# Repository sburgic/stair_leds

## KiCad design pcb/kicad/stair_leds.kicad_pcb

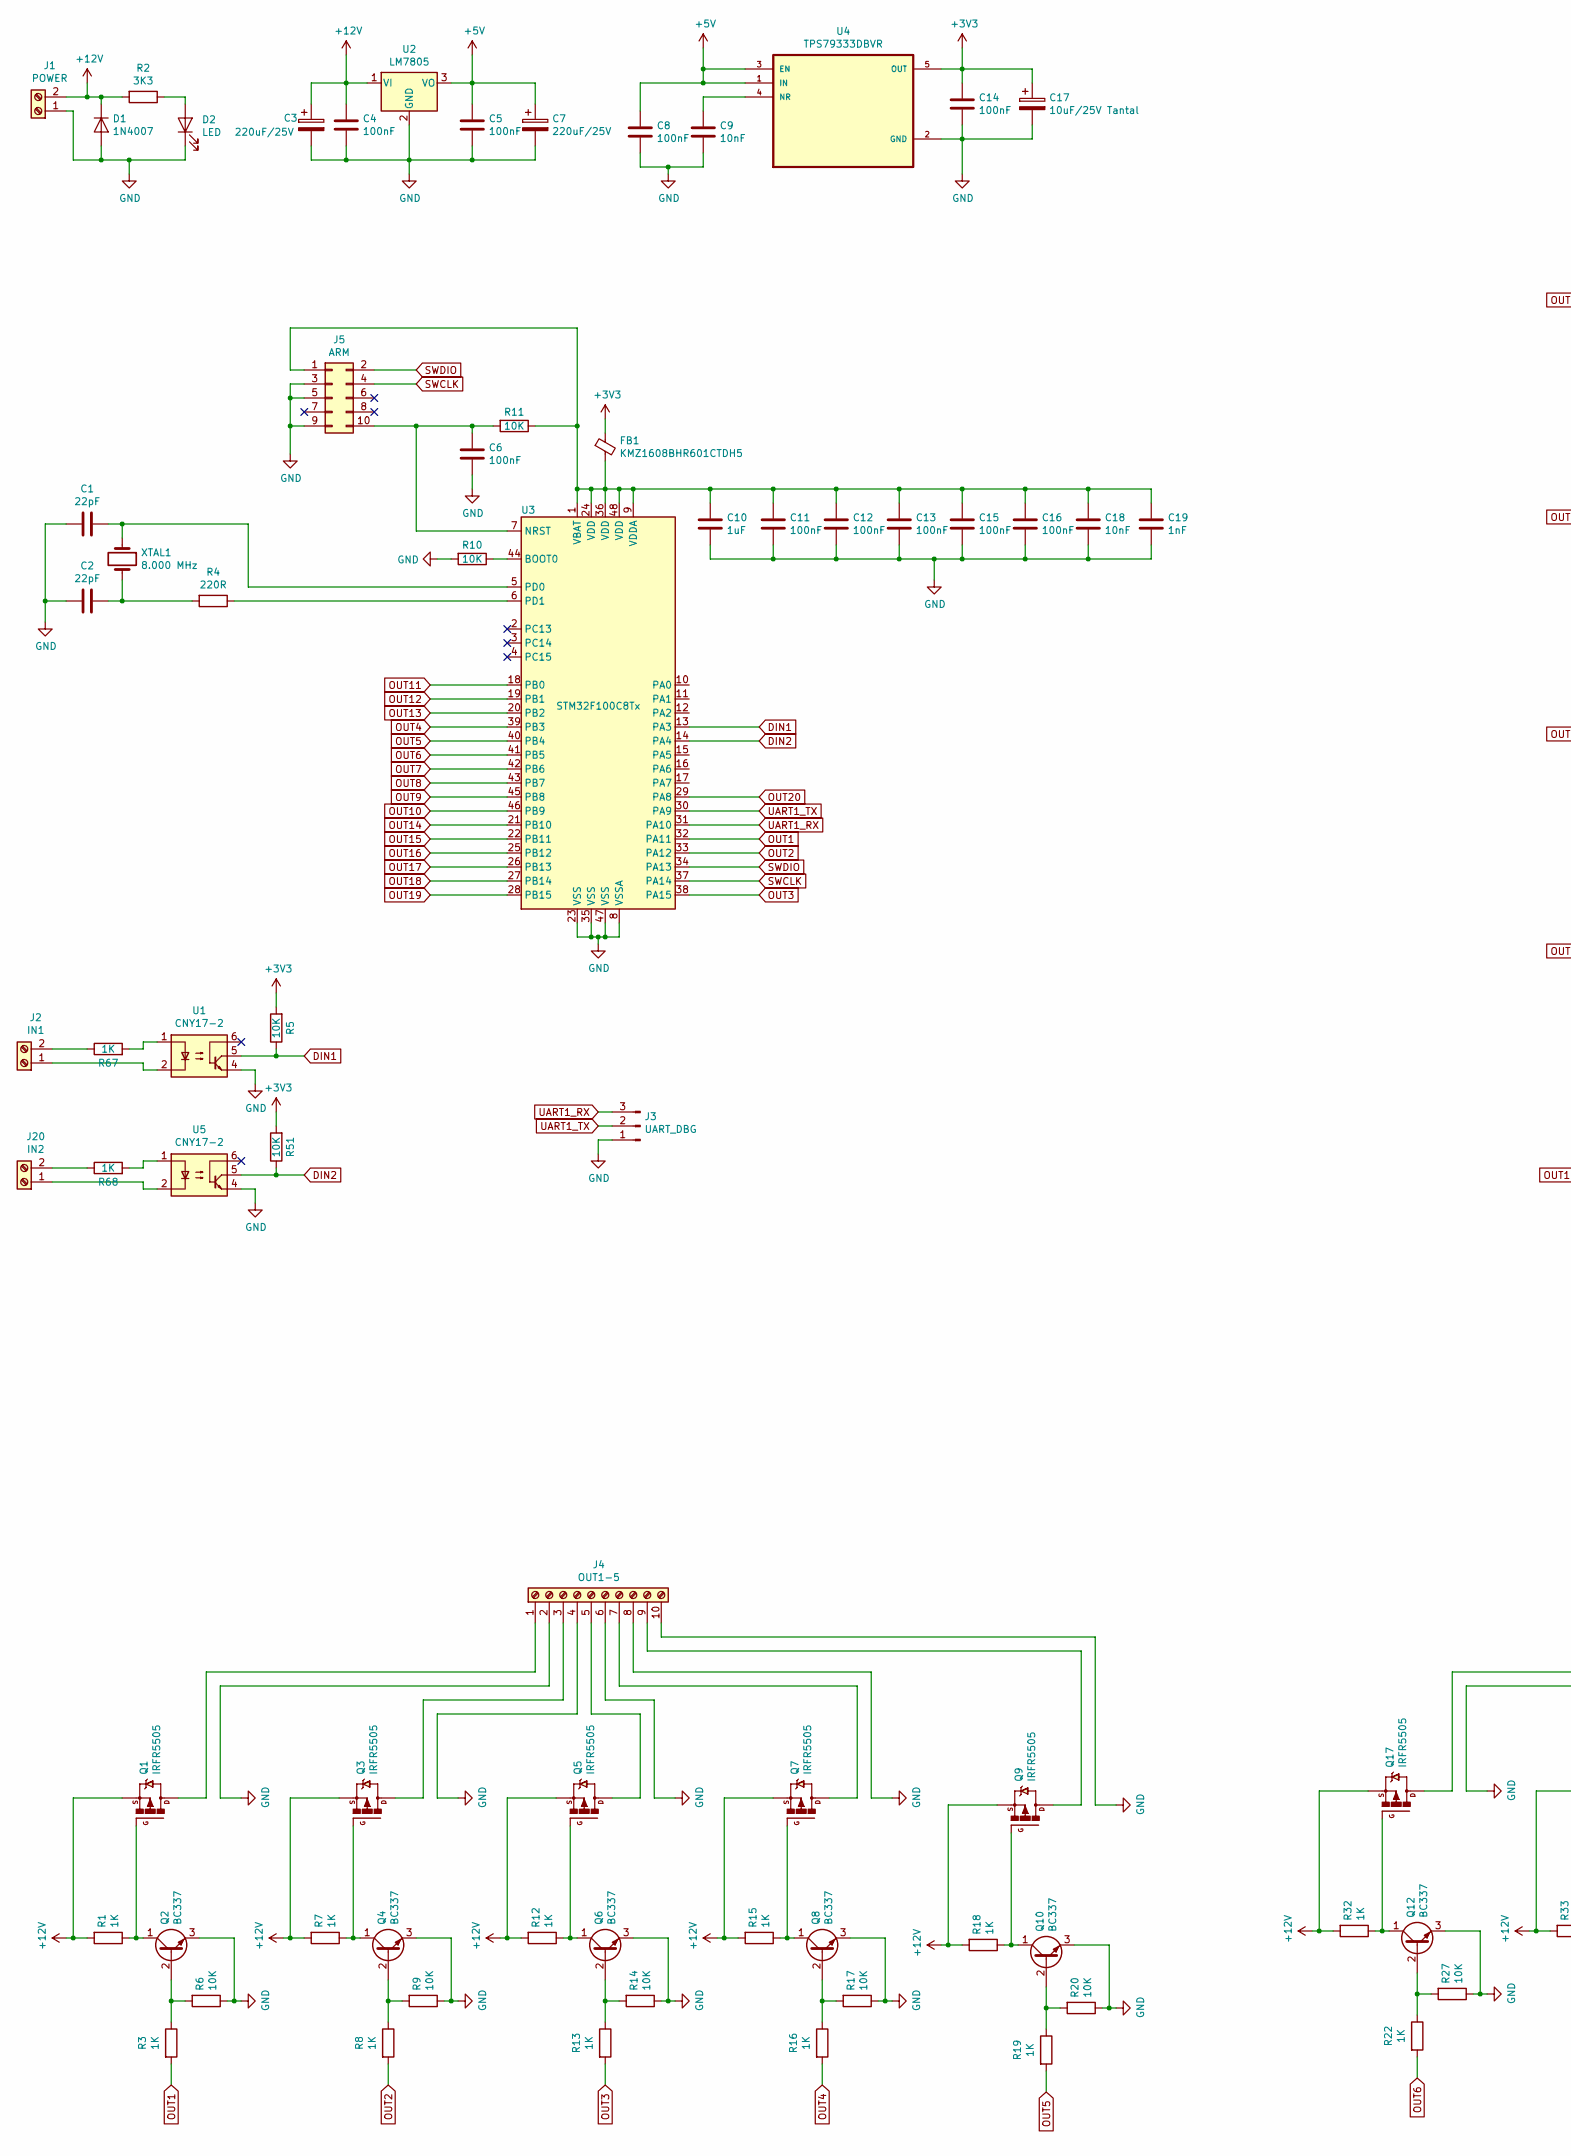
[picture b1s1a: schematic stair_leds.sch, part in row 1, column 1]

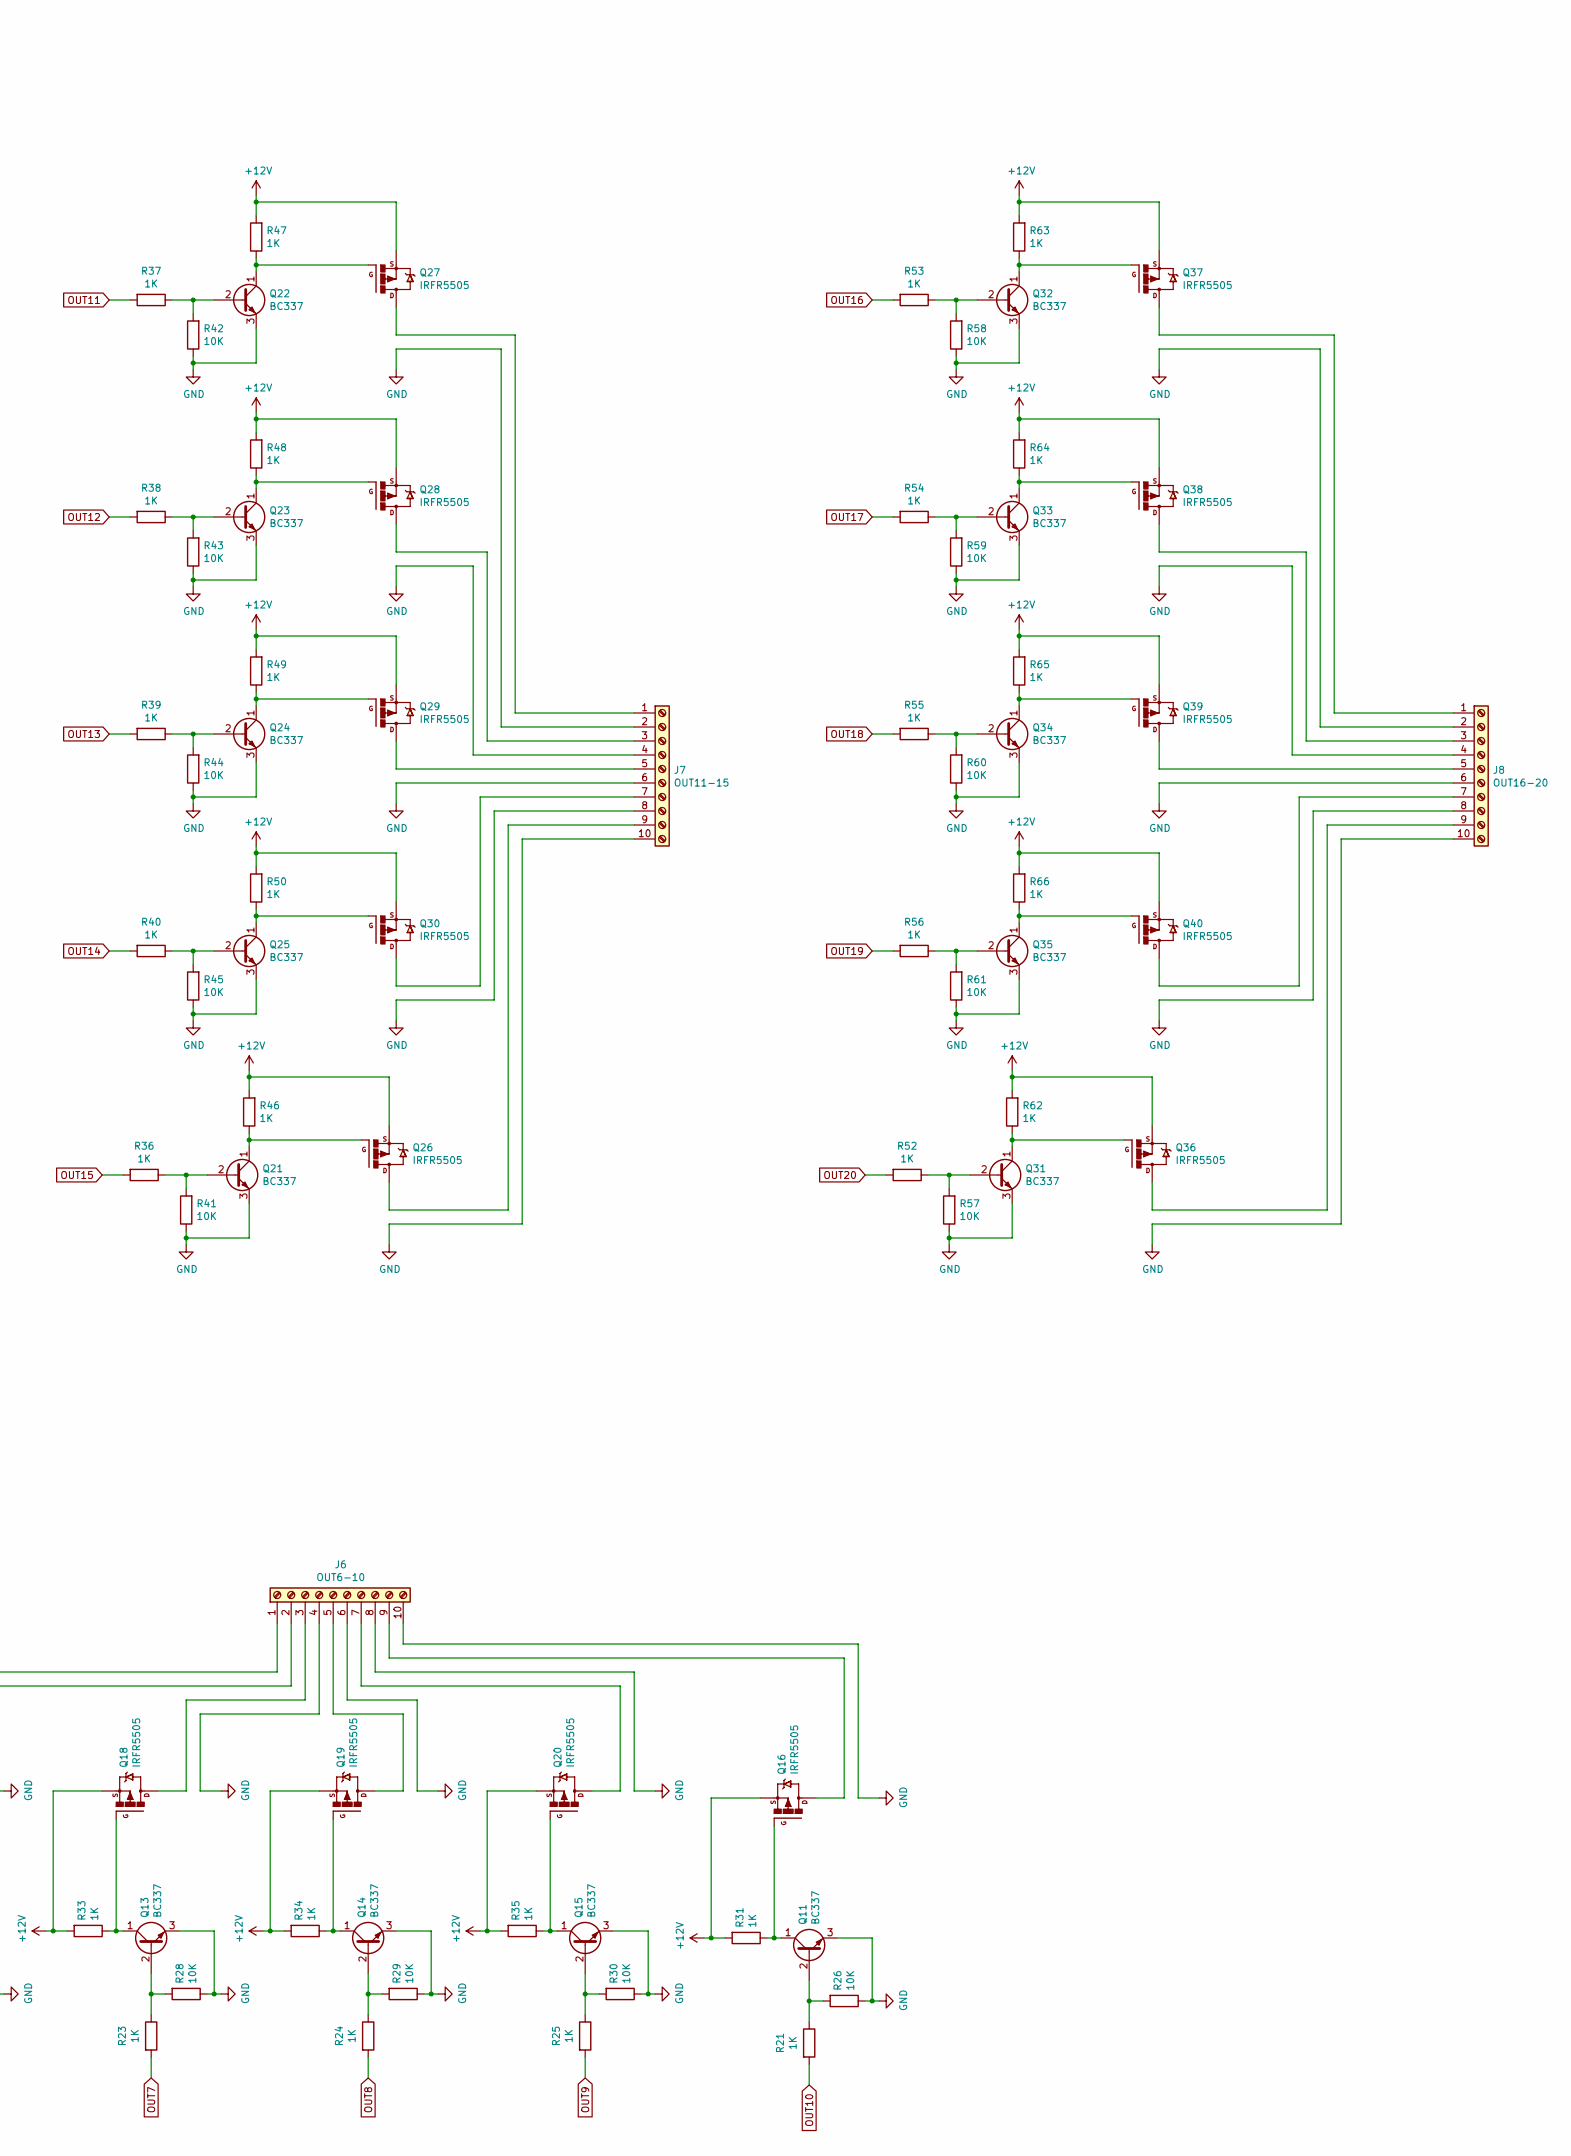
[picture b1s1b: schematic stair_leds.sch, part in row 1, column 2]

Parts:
C1, C2: 22pF; C_Disc_D3.0mm_W1.6mm_P2.50mm
C3, C7: 220uF/25V; CP_Radial_D10.0mm_P5.00mm
C4, C5, C6, C8, C11, C12, C13, C14, C15, C16: 100nF; C_0603_1608Metric_Pad1.05x0.95mm_HandSolder
C9, C18: 10nF; C_0603_1608Metric_Pad1.05x0.95mm_HandSolder
C10: 1uF; C_0805_2012Metric_Pad1.15x1.40mm_HandSolder
C17: 10uF/25V Tantal; C_1210_3225Metric_Pad1.42x2.65mm_HandSolder
C19: 1nF; C_0603_1608Metric_Pad1.05x0.95mm_HandSolder
D1: 1N4007; D_DO-41_SOD81_P10.16mm_Horizontal
D2: LED; LED_D3.0mm
FB1: KMZ1608BHR601CTDH5; C_0805_2012Metric_Pad1.15x1.40mm_HandSolder
J1: POWER; TerminalBlock_MetzConnect_Type011_RT05502HBWC_1x02_P5.00mm_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
J2: IN1; TerminalBlock_MetzConnect_Type011_RT05502HBWC_1x02_P5.00mm_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
J3: UART_DBG; PinHeader_1x03_P2.54mm_Vertical
J4: OUT1-5; TerminalBlock_RND_205-00009_1x10_P5.00mm_Horizontal
J5: ARM; PinHeader_2x05_P1.27mm_Vertical
J6: OUT6-10; TerminalBlock_RND_205-00009_1x10_P5.00mm_Horizontal
J7: OUT11-15; TerminalBlock_RND_205-00009_1x10_P5.00mm_Horizontal
J8: OUT16-20; TerminalBlock_RND_205-00009_1x10_P5.00mm_Horizontal
J20: IN2; TerminalBlock_MetzConnect_Type011_RT05502HBWC_1x02_P5.00mm_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
Q1, Q3, Q5, Q7, Q9, Q16, Q17, Q18, Q19, Q20, Q26, Q27, Q28, Q29, Q30, Q36, Q37, Q38, Q39, Q40: IRFR5505; DPAK
Q2, Q4, Q6, Q8, Q10, Q11, Q12, Q13, Q14, Q15, Q21, Q22, Q23, Q24, Q25, Q31, Q32, Q33, Q34, Q35: BC337; TO-92_Inline_Wide
R1, R3, R7, R8, R12, R13, R15, R16, R18, R19, R21, R22, R23, R24, R25, R31, R32, R33, R34, R35, R36, R37, R38, R39, R40, R46, R47, R48, R49, R50, R52, R53, R54, R55, R56, R62, R63, R64, R65, R66, R67, R68: 1K; R_0805_2012Metric_Pad1.15x1.40mm_HandSolder
R2: 3K3; R_0805_2012Metric_Pad1.15x1.40mm_HandSolder
R4: 220R; R_0805_2012Metric_Pad1.15x1.40mm_HandSolder
R5, R6, R9, R10, R11, R14, R17, R20, R26, R27, R28, R29, R30, R41, R42, R43, R44, R45, R51, R57, R58, R59, R60, R61: 10K; R_0805_2012Metric_Pad1.15x1.40mm_HandSolder
U1, U5: CNY17-2; DIP-6_W7.62mm
U2: LM7805; TO-220-3_Vertical
U3: STM32F100C8Tx; LQFP-48_7x7mm_P0.5mm
U4: TPS79333DBVR; SOT95P280X145-5N
XTAL1: 8.000 MHz; Crystal_SMD_HC49-SD

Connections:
+3V3: C14.1, C17.1, FB1.1, R5.2, R51.2, U4.5 (OUT)
+5V: C5.1, C7.1, C8.1, U2.3 (VO), U4.1 (IN), U4.3 (EN)
+12V: C3.1, C4.1, D1.1 (K), J1.2, Q1.3, Q3.3, Q5.3, Q7.3, Q9.3, Q16.3, Q17.3, Q18.3, Q19.3, Q20.3, Q26.3, Q27.3, Q28.3, Q29.3, Q30.3, Q36.3, Q37.3, Q38.3, Q39.3, Q40.3, R1.2, R2.2, R7.2, R12.2, R15.2, R18.2, R31.2, R32.2, R33.2, R34.2, R35.2, R46.2, R47.2, R48.2, R49.2, R50.2, R62.2, R63.2, R64.2, R65.2, R66.2, U2.1 (VI)
DIN1: R5.1, U1.5, U3.13 (PA3)
DIN2: R51.1, U3.14 (PA4), U5.5
GND: C1.2, C2.2, C3.2, C4.2, C5.2, C6.2, C7.2, C8.2, C9.2, C10.2, C11.2, C12.2, C13.2, C14.2, C15.2, C16.2, C17.2, C18.2, C19.2, D1.2 (A), D2.1 (K), J1.1, J3.1, J4.2, J4.4, J4.6, J4.8, J4.10, J5.3, J5.5, J5.9, J6.2, J6.4, J6.6, J6.8, J6.10, J7.2, J7.4, J7.6, J7.8, J7.10, J8.2, J8.4, J8.6, J8.8, J8.10, Q2.3 (E), Q4.3 (E), Q6.3 (E), Q8.3 (E), Q10.3 (E), Q11.3 (E), Q12.3 (E), Q13.3 (E), Q14.3 (E), Q15.3 (E), Q21.3 (E), Q22.3 (E), Q23.3 (E), Q24.3 (E), Q25.3 (E), Q31.3 (E), Q32.3 (E), Q33.3 (E), Q34.3 (E), Q35.3 (E), R6.1, R9.1, R10.2, R14.1, R17.1, R20.1, R26.1, R27.1, R28.1, R29.1, R30.1, R41.1, R42.1, R43.1, R44.1, R45.1, R57.1, R58.1, R59.1, R60.1, R61.1, U1.4, U2.2 (GND), U3.8 (VSSA), U3.23 (VSS), U3.35 (VSS), U3.47 (VSS), U4.2 (GND), U5.4
unnamed: C1.1, U3.5 (PD0), XTAL1.1
unnamed: C2.1, R4.2, XTAL1.2
unnamed: C6.1, J5.10, R11.2, U3.7 (NRST)
unnamed: C9.1, U4.4 (NR)
unnamed: C10.1, C11.1, C12.1, C13.1, C15.1, C16.1, C18.1, C19.1, FB1.2, J5.1, R11.1, U3.1 (VBAT), U3.9 (VDDA), U3.24 (VDD), U3.36 (VDD), U3.48 (VDD)
unnamed: D2.2 (A), R2.1
unnamed: J2.1, U1.2
unnamed: J2.2, R67.1
unnamed: J4.1, Q1.4
unnamed: J4.3, Q3.4
unnamed: J4.5, Q5.4
unnamed: J4.7, Q7.4
unnamed: J4.9, Q9.4
unnamed: J6.1, Q17.4
unnamed: J6.3, Q18.4
unnamed: J6.5, Q19.4
unnamed: J6.7, Q20.4
unnamed: J6.9, Q16.4
unnamed: J7.1, Q27.4
unnamed: J7.3, Q28.4
unnamed: J7.5, Q29.4
unnamed: J7.7, Q30.4
unnamed: J7.9, Q26.4
unnamed: J8.1, Q37.4
unnamed: J8.3, Q38.4
unnamed: J8.5, Q39.4
unnamed: J8.7, Q40.4
unnamed: J8.9, Q36.4
unnamed: J20.1, U5.2
unnamed: J20.2, R68.1
unnamed: Q1.1, Q2.1 (C), R1.1
unnamed: Q2.2 (B), R3.1, R6.2
unnamed: Q3.1, Q4.1 (C), R7.1
unnamed: Q4.2 (B), R8.1, R9.2
unnamed: Q5.1, Q6.1 (C), R12.1
unnamed: Q6.2 (B), R13.1, R14.2
unnamed: Q7.1, Q8.1 (C), R15.1
unnamed: Q8.2 (B), R16.1, R17.2
unnamed: Q9.1, Q10.1 (C), R18.1
unnamed: Q10.2 (B), R19.1, R20.2
unnamed: Q11.1 (C), Q16.1, R31.1
unnamed: Q11.2 (B), R21.1, R26.2
unnamed: Q12.1 (C), Q17.1, R32.1
unnamed: Q12.2 (B), R22.1, R27.2
unnamed: Q13.1 (C), Q18.1, R33.1
unnamed: Q13.2 (B), R23.1, R28.2
unnamed: Q14.1 (C), Q19.1, R34.1
unnamed: Q14.2 (B), R24.1, R29.2
unnamed: Q15.1 (C), Q20.1, R35.1
unnamed: Q15.2 (B), R25.1, R30.2
unnamed: Q21.1 (C), Q26.1, R46.1
unnamed: Q21.2 (B), R36.1, R41.2
unnamed: Q22.1 (C), Q27.1, R47.1
unnamed: Q22.2 (B), R37.1, R42.2
unnamed: Q23.1 (C), Q28.1, R48.1
unnamed: Q23.2 (B), R38.1, R43.2
unnamed: Q24.1 (C), Q29.1, R49.1
unnamed: Q24.2 (B), R39.1, R44.2
unnamed: Q25.1 (C), Q30.1, R50.1
unnamed: Q25.2 (B), R40.1, R45.2
unnamed: Q31.1 (C), Q36.1, R62.1
unnamed: Q31.2 (B), R52.1, R57.2
unnamed: Q32.1 (C), Q37.1, R63.1
unnamed: Q32.2 (B), R53.1, R58.2
unnamed: Q33.1 (C), Q38.1, R64.1
unnamed: Q33.2 (B), R54.1, R59.2
unnamed: Q34.1 (C), Q39.1, R65.1
unnamed: Q34.2 (B), R55.1, R60.2
unnamed: Q35.1 (C), Q40.1, R66.1
unnamed: Q35.2 (B), R56.1, R61.2
unnamed: R4.1, U3.6 (PD1)
unnamed: R10.1, U3.44 (BOOT0)
unnamed: R67.2, U1.1
unnamed: R68.2, U5.1
OUT1: R3.2, U3.32 (PA11)
OUT2: R8.2, U3.33 (PA12)
OUT3: R13.2, U3.38 (PA15)
OUT4: R16.2, U3.39 (PB3)
OUT5: R19.2, U3.40 (PB4)
OUT6: R22.2, U3.41 (PB5)
OUT7: R23.2, U3.42 (PB6)
OUT8: R24.2, U3.43 (PB7)
OUT9: R25.2, U3.45 (PB8)
OUT10: R21.2, U3.46 (PB9)
OUT11: R37.2, U3.18 (PB0)
OUT12: R38.2, U3.19 (PB1)
OUT13: R39.2, U3.20 (PB2)
OUT14: R40.2, U3.21 (PB10)
OUT15: R36.2, U3.22 (PB11)
OUT16: R53.2, U3.25 (PB12)
OUT17: R54.2, U3.26 (PB13)
OUT18: R55.2, U3.27 (PB14)
OUT19: R56.2, U3.28 (PB15)
OUT20: R52.2, U3.29 (PA8)
SWCLK: J5.4, U3.37 (PA14)
SWDIO: J5.2, U3.34 (PA13)
UART1_RX: J3.3, U3.31 (PA10)
UART1_TX: J3.2, U3.30 (PA9)

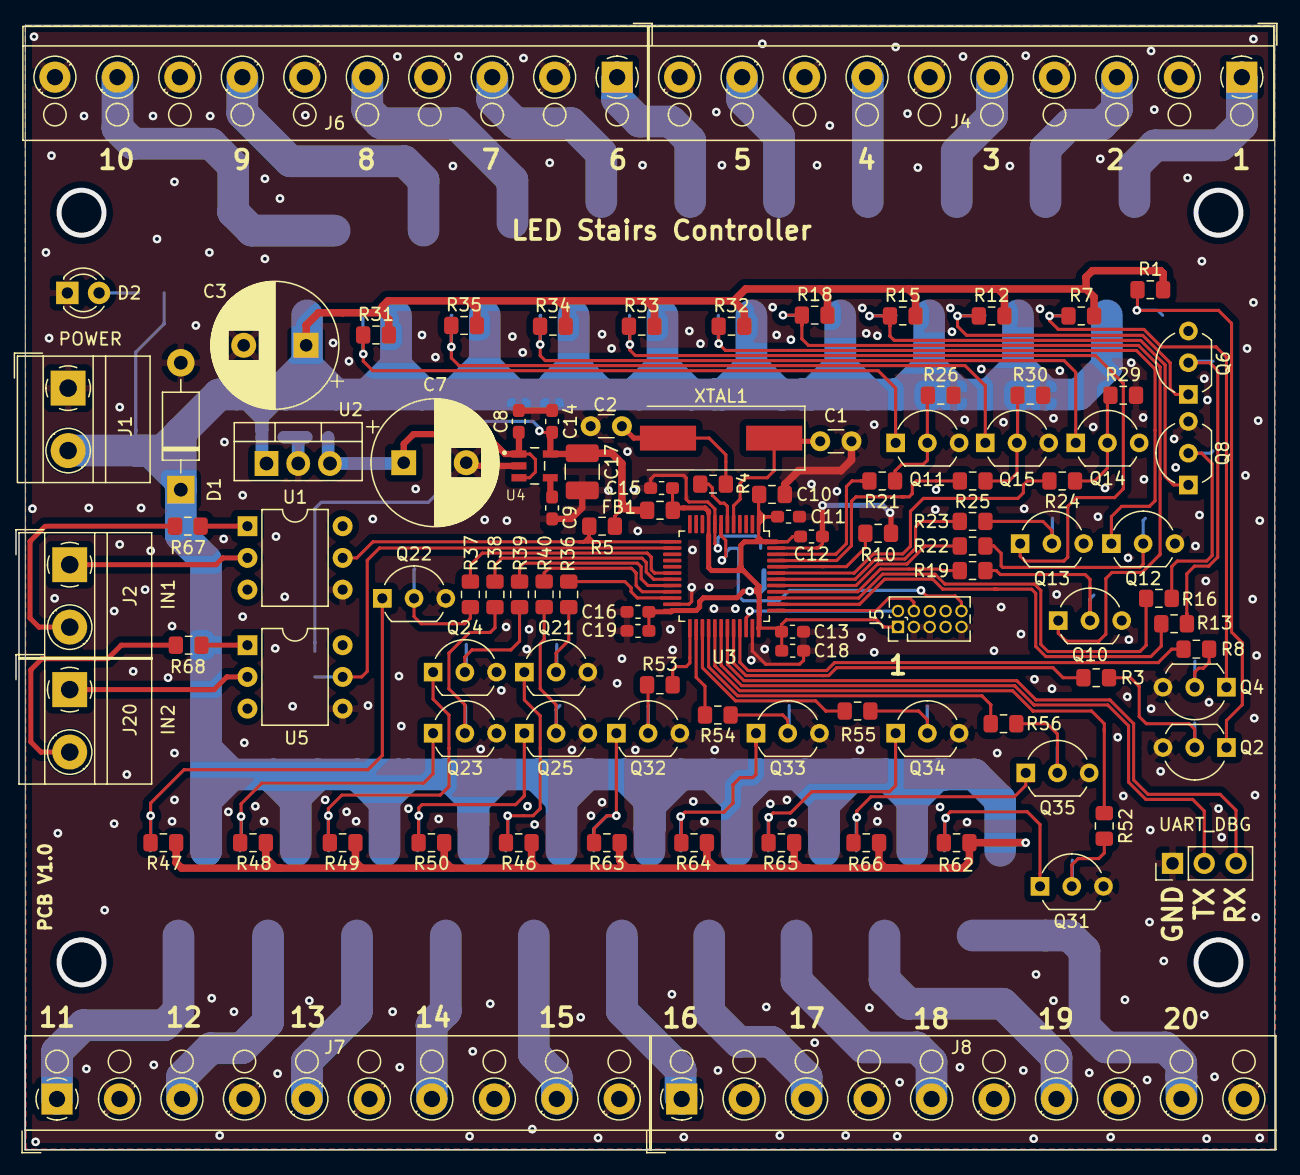
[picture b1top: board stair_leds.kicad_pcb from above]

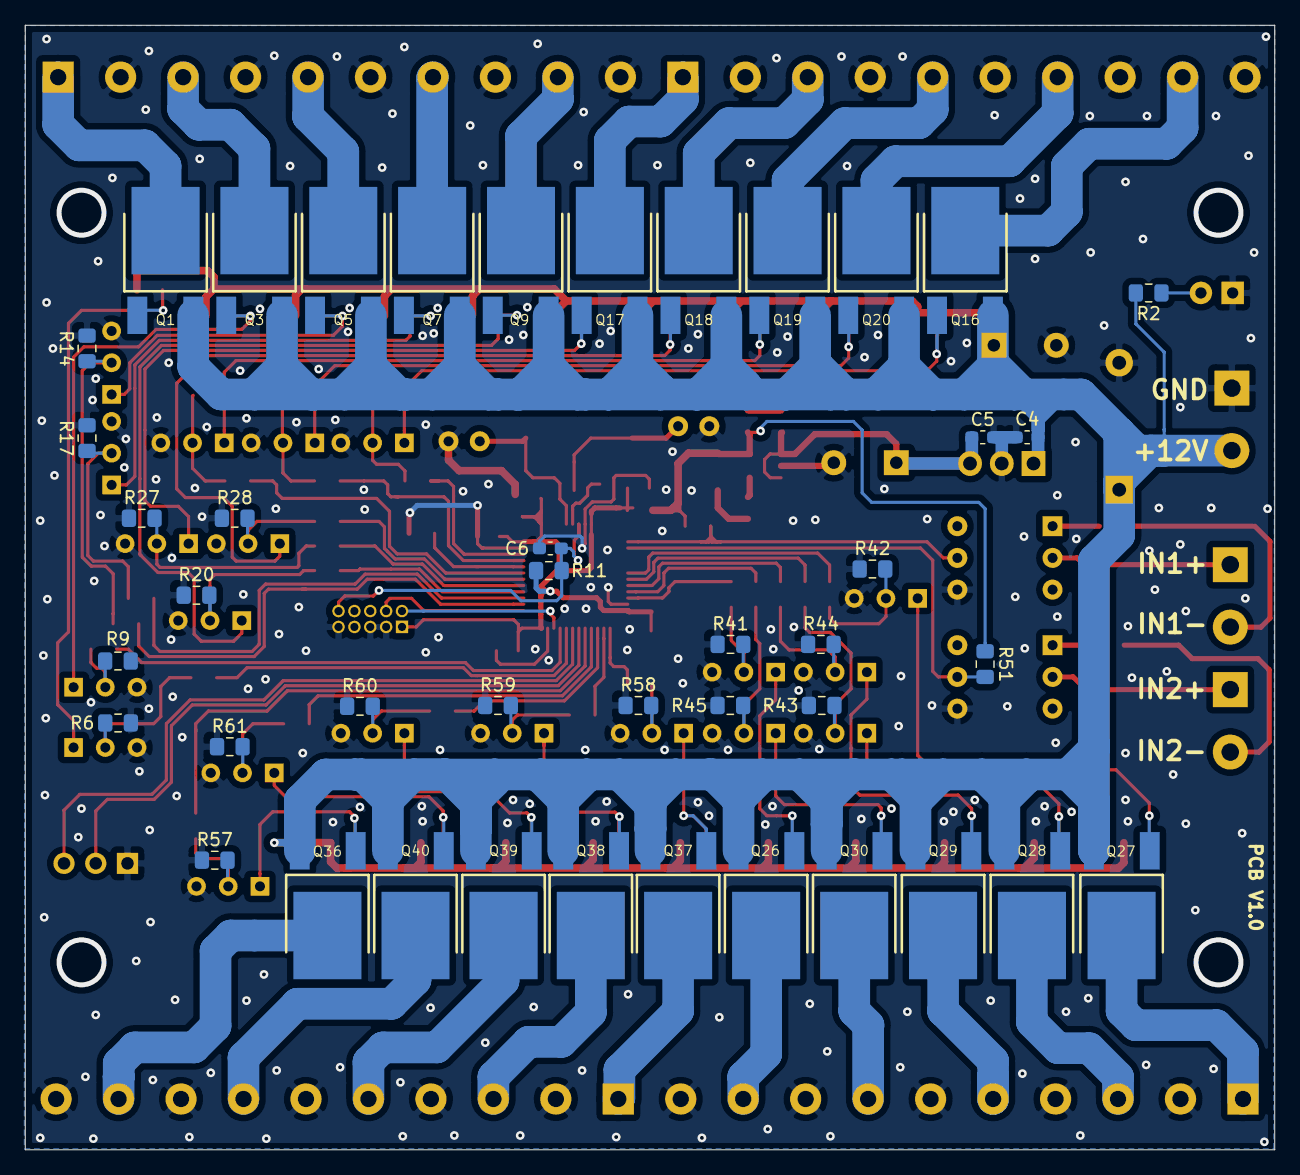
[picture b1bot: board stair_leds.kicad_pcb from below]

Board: 2 copper layers, 100.0 x 90.0 mm, 145 parts (43 on the bottom side), 104 nets.

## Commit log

2020-12-19 add .gitignore
2020-12-19 add pcb ver1.0
